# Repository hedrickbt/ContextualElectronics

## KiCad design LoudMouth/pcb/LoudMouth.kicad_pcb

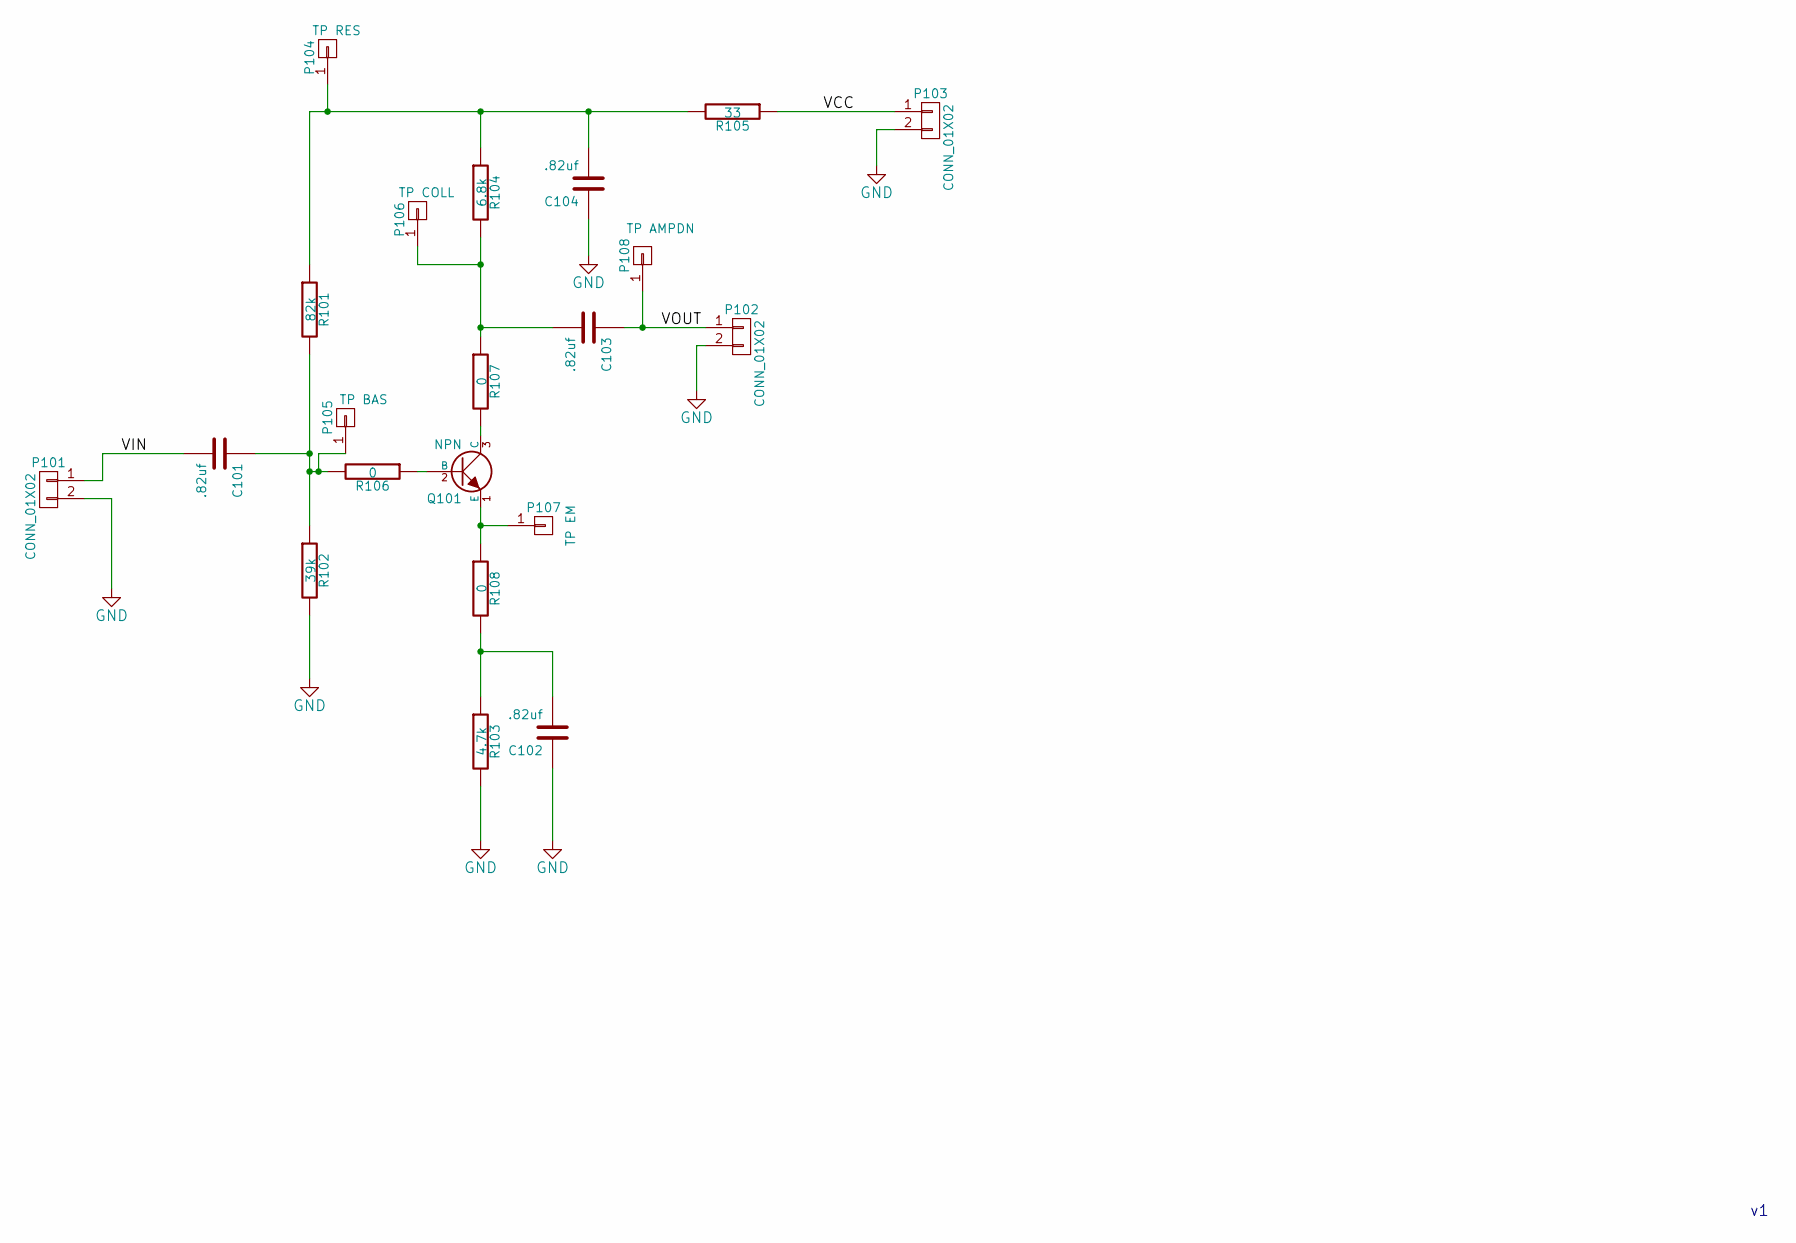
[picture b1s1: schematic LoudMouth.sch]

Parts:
C101, C102: .82uf; C_1210_HandSoldering; MPN Value
C103, C104: .82uf; C_1210_HandSoldering
P101, P102, P103: CONN_01X02; Pin_Header_Straight_1x02
P104: TP RES; TESTPOINT_1
P105: TP BAS; TESTPOINT_1
P106: TP COLL; TESTPOINT_1
P107: TP EM; TESTPOINT_1
P108: TP AMPDN; TESTPOINT_1; MPN Value
Q101: NPN; TO-92_Molded_Narrow
R101: 82k; R_0805_HandSoldering
R102: 39k; R_0805_HandSoldering; MPN Value
R103: 4.7k; R_0805_HandSoldering
R104: 6.8k; R_0805_HandSoldering
R105: 33; R_0805_HandSoldering
R106, R108: 0; R_0805_HandSoldering; MPN Value
R107: 0; R_0805_HandSoldering

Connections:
/VCC: P103.1, R105.1
/VIN: C101.2, P101.1
/VOUT: C103.1, P102.1, P108.1
GND: C102.1, C104.1, P101.2, P102.2, P103.2, R102.2, R103.2
unnamed: C101.1, P105.1, R101.2, R102.1, R106.2
unnamed: C102.2, R103.1, R108.2
unnamed: C103.2, P106.1, R104.2, R107.1
unnamed: C104.2, P104.1, R101.1, R104.1, R105.2
unnamed: P107.1, Q101.1 (E), R108.1
unnamed: Q101.2 (B), R106.1
unnamed: Q101.3 (C), R107.2

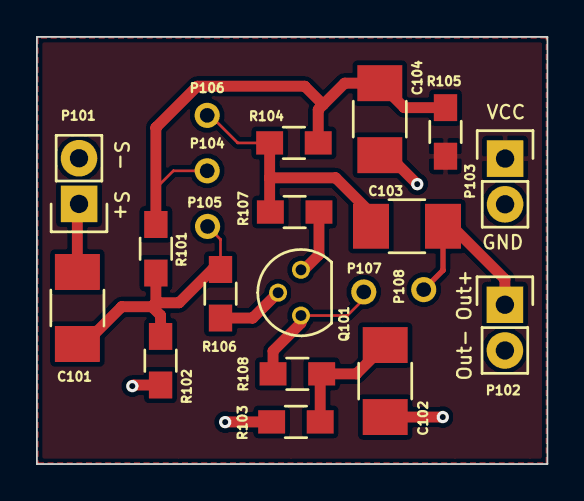
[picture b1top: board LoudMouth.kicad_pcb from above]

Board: 2 copper layers, 28.4 x 23.7 mm, 21 parts (0 on the bottom side), 11 nets.

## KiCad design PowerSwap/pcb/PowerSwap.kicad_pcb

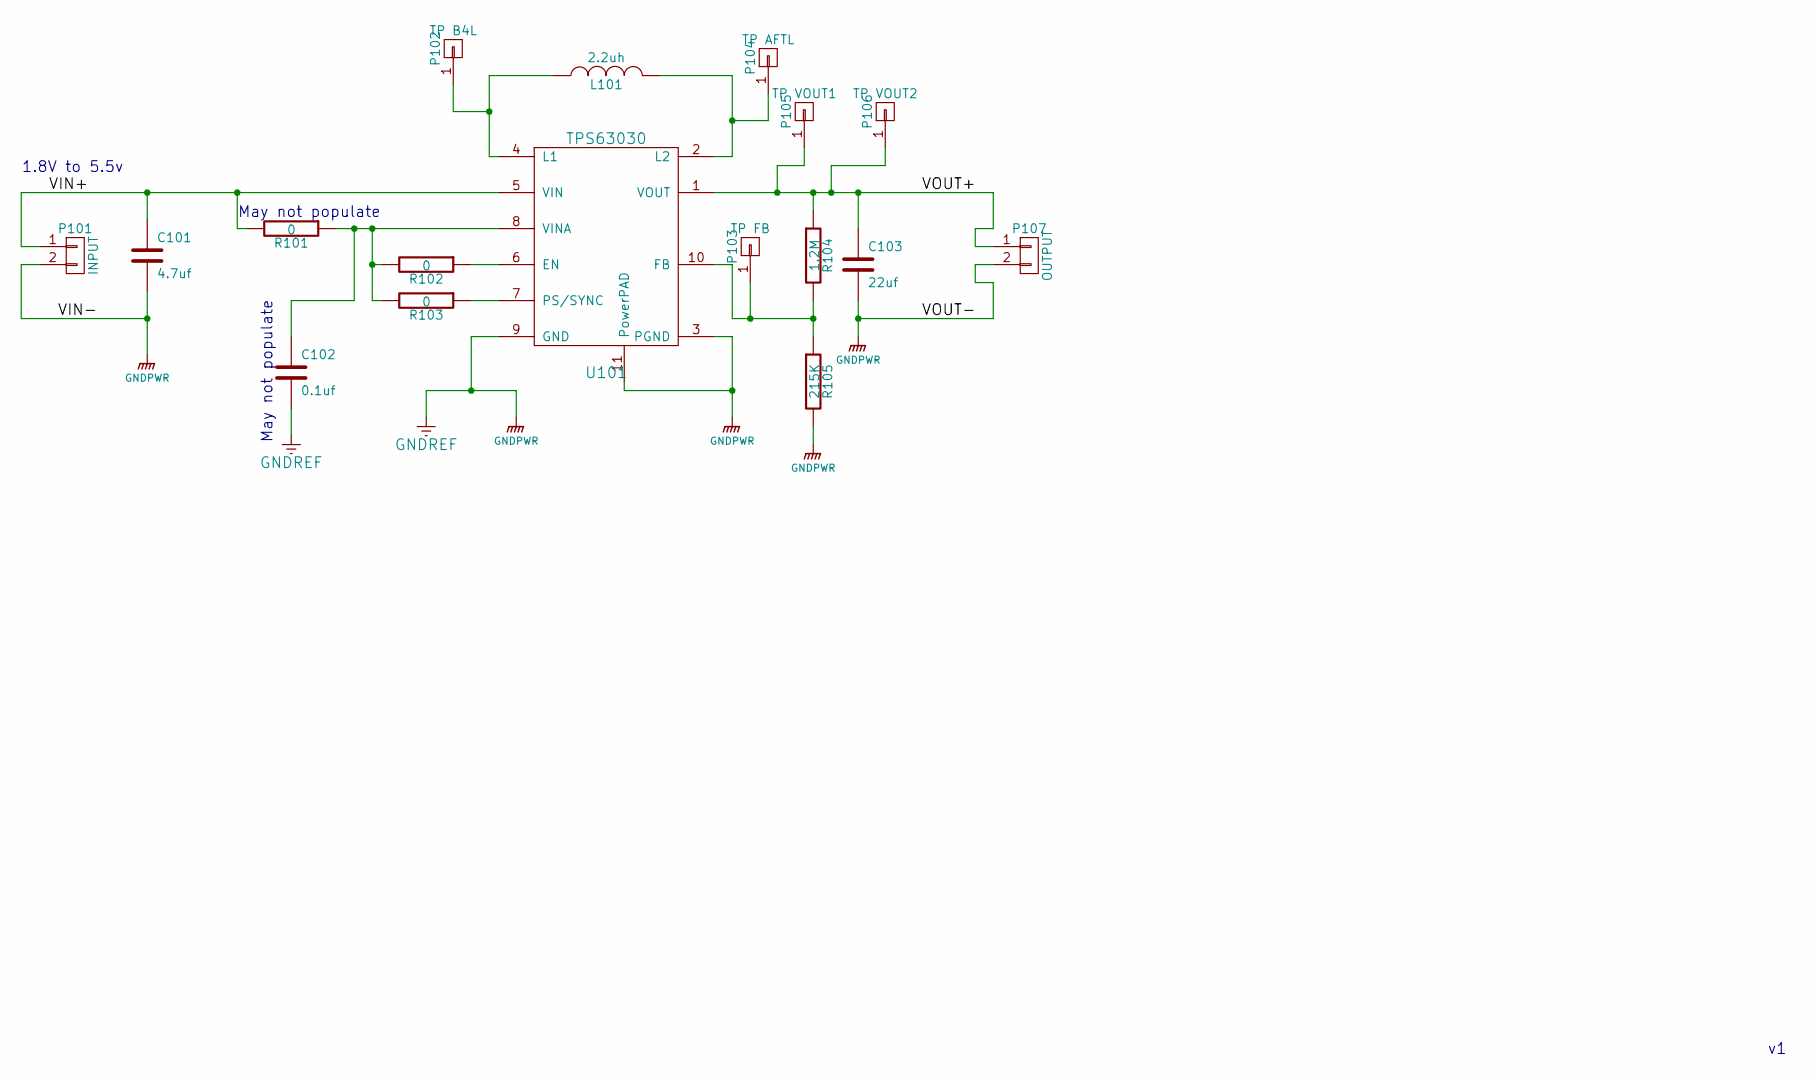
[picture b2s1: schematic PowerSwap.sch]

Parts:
C101: 4.7uf; MPN Value
C102: 0.1uf; MPN Value
C103: 22uf; MPN Value
L101: 2.2uh; LQH3NPN2R2NG0; MPN LQH3NPN2R2NG0
P101: INPUT
P102: TP B4L
P103: TP FB
P104: TP AFTL
P105: TP VOUT1
P106: TP VOUT2
P107: OUTPUT
R101: 0; MPN Value
R102, R103: 0
R104: 1.2M; MPN Value
R105: 215K
U101: TPS63030; SON10_HandSoldered_TPS63030

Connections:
/VIN+: C101.1, P101.1, R101.2, U101.5 (VIN)
/VOUT+: C103.1, P105.1, P106.1, P107.1, R104.1, U101.1 (VOUT); also elsewhere on the board
GNDPWR: C101.2, C102.2, C103.2, P101.2, P107.2, R105.2, U101.3 (PGND), U101.9 (GND), U101.11 (PowerPAD); also elsewhere on the board
unnamed: C102.1, R101.1, R102.2, R103.2, U101.8 (VINA)
unnamed: L101.1, P102.1, U101.4 (L1)
unnamed: L101.2, P104.1, U101.2 (L2)
unnamed: P103.1, R104.2, R105.1, U101.10 (FB)
unnamed: R102.1, U101.6 (EN)
unnamed: R103.1, U101.7 (PS/SYNC)

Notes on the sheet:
1.8V to 5.5v
May not populate

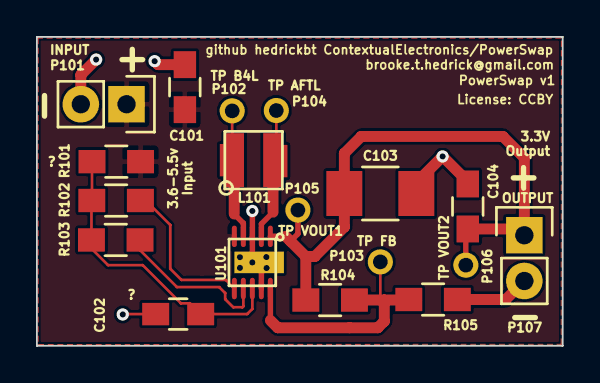
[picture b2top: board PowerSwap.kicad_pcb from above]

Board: 2 copper layers, 29.2 x 17.2 mm, 18 parts (0 on the bottom side), 9 nets.

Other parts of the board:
C104: uf; C_0805_HandSoldering

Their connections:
/VOUT+: C104.1; also elsewhere on the board
GNDPWR: C104.2; also elsewhere on the board

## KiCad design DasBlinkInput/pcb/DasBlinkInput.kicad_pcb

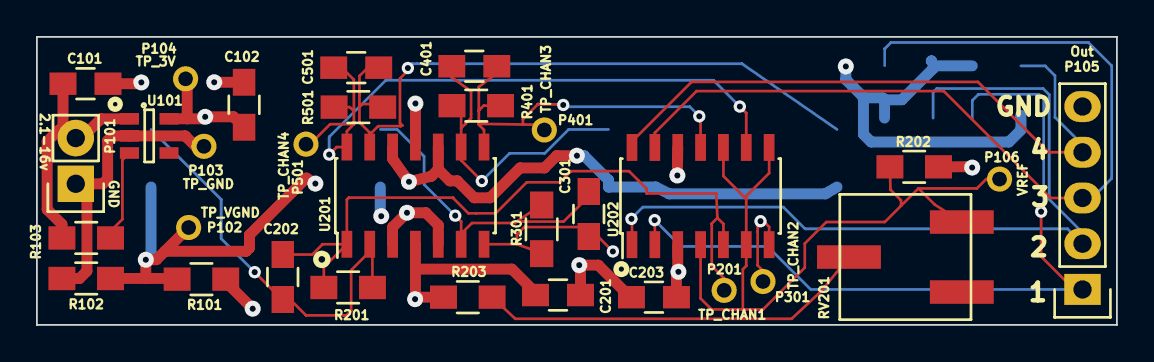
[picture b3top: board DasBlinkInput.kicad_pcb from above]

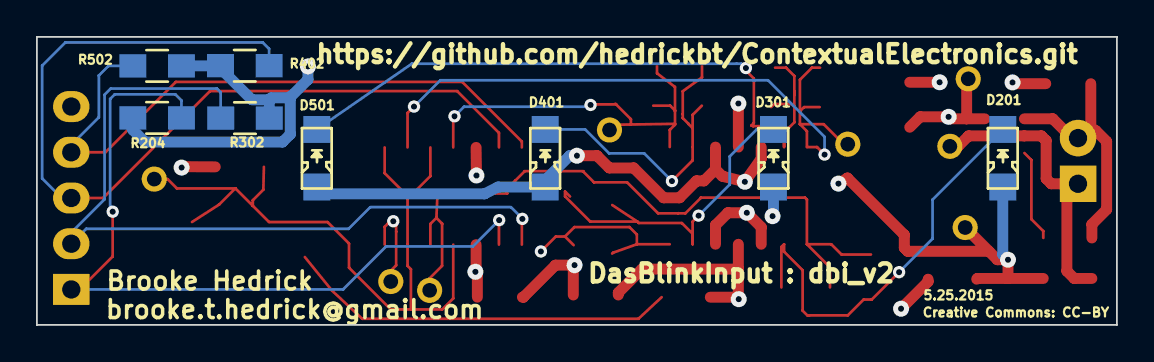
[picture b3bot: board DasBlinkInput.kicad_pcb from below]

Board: 4 copper layers, 60.0 x 16.0 mm, 39 parts (8 on the bottom side), 19 nets.

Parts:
C101, C102: 1uf; C_0805_HandSoldering
C201, C203: .1uf; C_0805_HandSoldering
C202, C301, C401, C501: 100pf; C_0805_HandSoldering
D201, D301, D401, D501: SFH 2701; SFH2701
P101: CONN_01X02; Pin_Header_Straight_1x02
P102: TP_VGND; TESTPOINT_1
P103: TP_GND; TESTPOINT_1
P104: TP_3V; TESTPOINT_1
P105: CONN_01X05; Pin_Header_Straight_1x05
P106: VREF; TESTPOINT_1
P201: TP_CHAN1; TESTPOINT_1
P301: TP_CHAN2; TESTPOINT_1
P401: TP_CHAN3; TESTPOINT_1
P501: TP_CHAN4; TESTPOINT_1
R101, R102, R202, R204, R302, R402, R502: 10K; R_0805_HandSoldering
R103, R203: 0; R_0805_HandSoldering
R201, R301, R401, R501: 1MEG; R_0805_HandSoldering
RV201: 10K; BOURNS_3361P
U101: LP2980-N; SOT-23-5
U201: MCP6404; SOIC-14_3.9x8.7mm_Pitch1.27mm
U202: LM339; SOIC-14_3.9x8.7mm_Pitch1.27mm

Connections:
3V: C102.1, C201.2, C203.2, P104.1, R101.1, R203.1, R204.1, R302.1, R402.1, R502.1, U101.5, U201.4, U202.3
/Channel1Photodetect/CHAN1_OUT: P105.1, R204.2, U202.2
/Channel2Photodetect/CHAN2_OUT: P105.2, R302.2, U202.1
/Channel2Photodetect/REF_IN: P106.1, R202.1, RV201.3, U202.4, U202.6, U202.8, U202.10
/Channel3Photodetect/CHAN3_OUT: P105.3, R402.2, U202.13
/Channel4Photodetect/CHAN4_OUT: P105.4, R502.2, U202.14
GND: C101.2, C102.2, C201.1, C203.1, P101.1, P103.1, P105.5, R102.2, R202.2, U101.2, U201.11, U202.12
unnamed: C101.1, P101.2, R103.1, U101.1
unnamed: C202.1, P201.1, R201.1, U201.1, U202.5
unnamed: C202.2, D201.2, R201.2, U201.2
unnamed: C301.1, P301.1, R301.1, U201.7, U202.7
unnamed: C301.2, D301.2, R301.2, U201.6
unnamed: C401.1, P401.1, R401.1, U201.8, U202.11
unnamed: C401.2, D401.2, R401.2, U201.9
unnamed: C501.1, P501.1, R501.1, U201.14, U202.9
unnamed: C501.2, D501.2, R501.2, U201.13
unnamed: R103.2, U101.3
unnamed: R203.2, RV201.2
VGND: D201.1, D301.1, D401.1, D501.1, P102.1, R101.2, R102.1, U201.3, U201.5, U201.10, U201.12

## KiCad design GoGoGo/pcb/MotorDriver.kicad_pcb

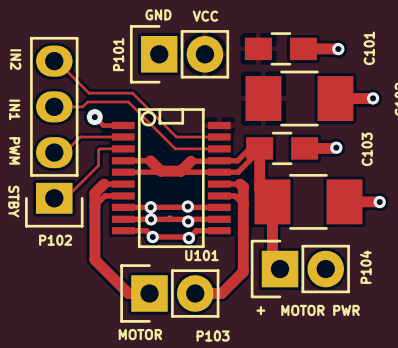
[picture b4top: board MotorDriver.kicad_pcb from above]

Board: 2 copper layers, 9 parts (0 on the bottom side), 9 nets.

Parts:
C101, C103: 0.1uf; C_0805_HandSoldering
C102, C104: 10uf; C_1210_HandSoldering
P101, P103, P104: CONN_01X02; Pin_Header_Straight_1x02
P102: CONN_01X04; Pin_Header_Straight_1x04
U101: TB6593FNG; SSOP-20

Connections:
/IN1: P102.3, U101.18
/IN2: P102.4, U101.19
/M+: P103.1, U101.6, U101.7
/PM+: C103.1, C104.1, P104.1, U101.4, U101.5, U101.16, U101.17
/PWM: P102.2, U101.2
/STBY: P102.1, U101.3
GND: C101.2, C102.2, C103.2, C104.2, P101.1, P104.2, U101.1, U101.8, U101.9, U101.10, U101.11, U101.12, U101.13
unnamed: C101.1, C102.1, P101.2, U101.20
unnamed: P103.2, U101.14, U101.15

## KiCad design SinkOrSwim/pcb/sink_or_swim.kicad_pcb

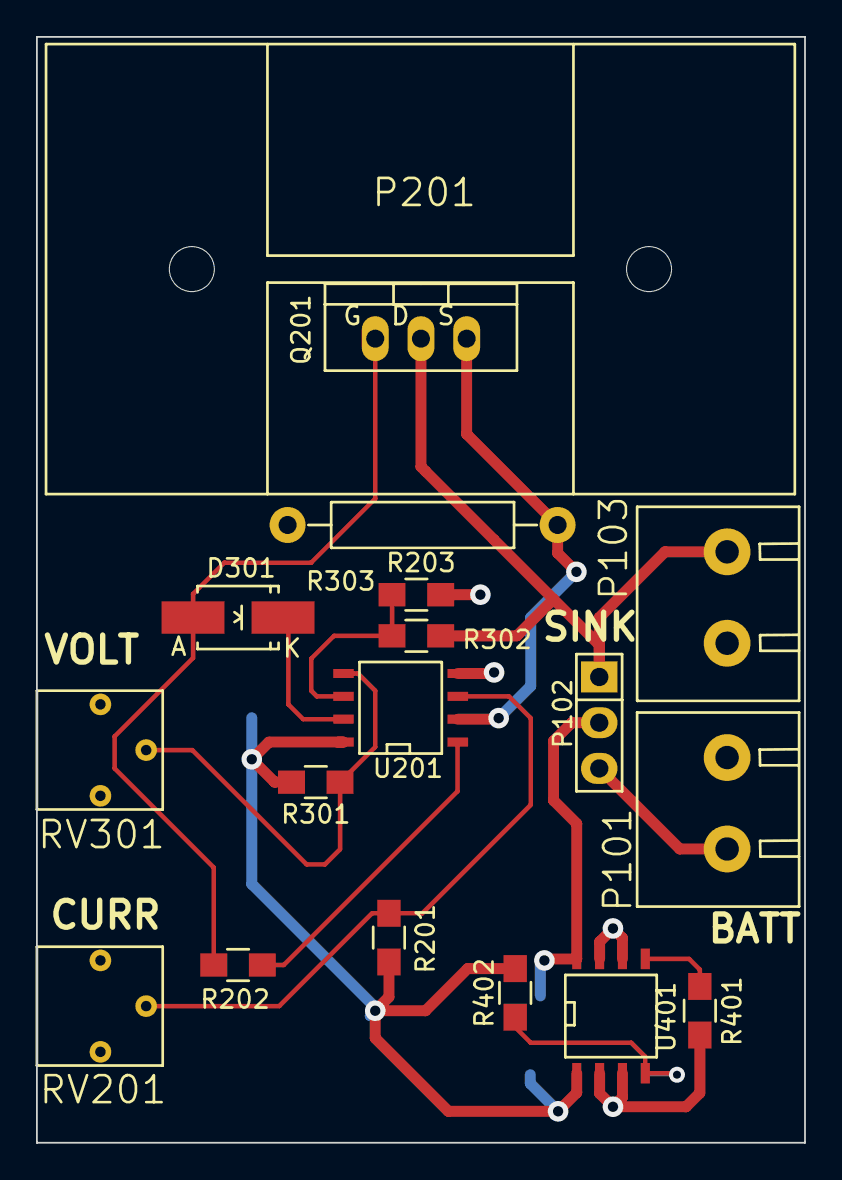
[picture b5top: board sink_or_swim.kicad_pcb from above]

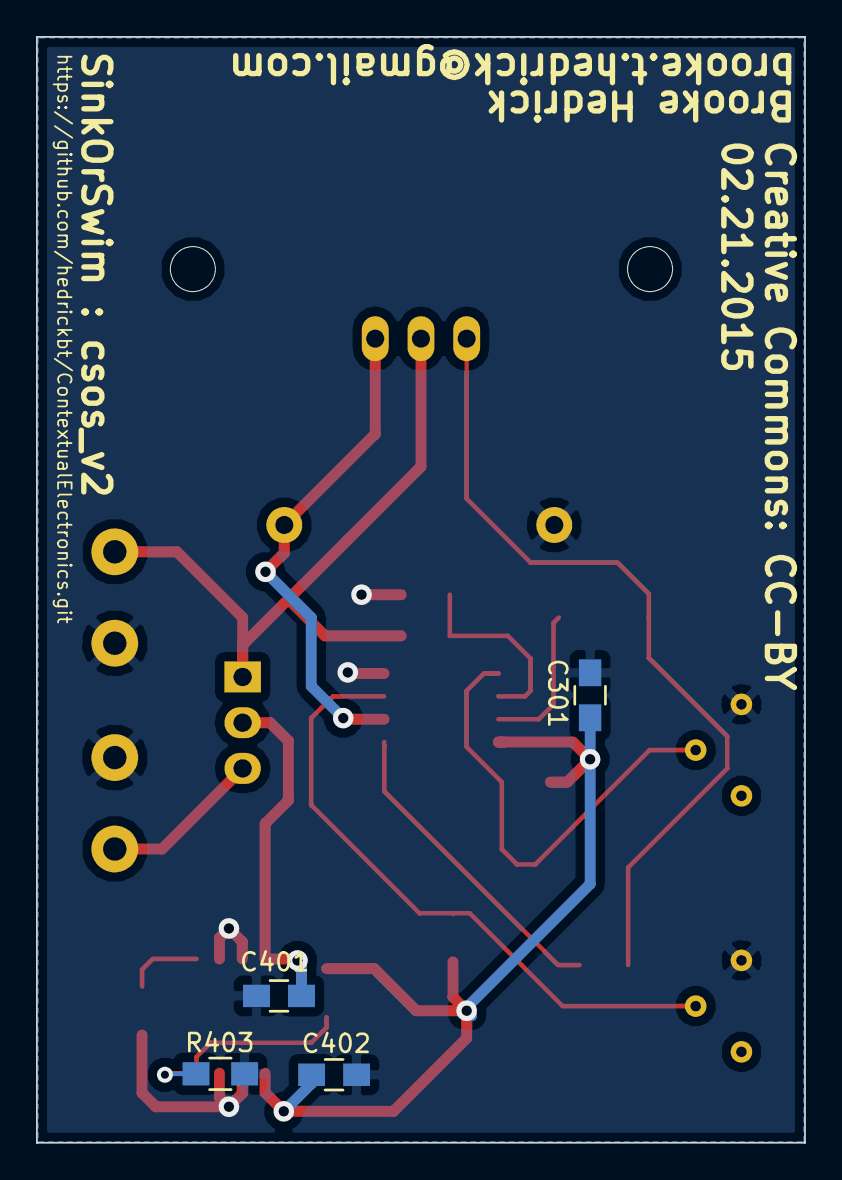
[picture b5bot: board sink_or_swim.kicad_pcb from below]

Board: 2 copper layers, 42.7 x 61.4 mm, 22 parts (4 on the bottom side), 14 nets.

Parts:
C301, C401, C402: .1uf; C_0805_HandSoldering
D301: DIODE; Diode-SMA_Handsoldering
P101, P103: TERMINAL_BLOCK; OSTTA024163
P102: CONN_01X03; Pin_Header_Straight_1x03
P201: HEATSINK; FA-T220-38E
Q201: BUK9575-100A; TO-220_FET-GDS_Vertical
R201: 68K; R_0805_HandSoldering
R202, R303: 1K; R_0805_HandSoldering
R203: .1; Resistor_Horizontal_RM15mm
R301: 28.7K; R_0805_HandSoldering
R302: 9K; R_0805_HandSoldering
R401: 0; R_0805_HandSoldering
R402: 27K; R_0805_HandSoldering
R403: 21.6K; R_0805_HandSoldering
RV201, RV301: 10K; Potiometer_Bourns_3362P
U201: LMV358; SOIC-8-N
U401: LM2931; SOIC-8-N

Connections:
2.7V: C301.1, C402.1, R201.1, R301.1, R402.2, U201.8, U401.1
/CurrentControl/Current_Sink+: P102.1, P103.2, Q201.D, R302.1
/CurrentControl/FET_Gate: D301.1, Q201.G, R202.1
/Power Regulation/Vin: C401.1, P102.2, U401.8
GND: C301.2, C401.2, C402.2, P101.2, P103.1, R203.2, R303.2, R401.2, R403.2, RV201.3, RV301.3, U201.4, U401.2, U401.3, U401.6, U401.7
unnamed: D301.2, U201.7
unnamed: P101.1, P102.3
unnamed: Q201.S, R203.1, U201.2
unnamed: R201.2, RV201.2, U201.3
unnamed: R202.2, U201.1
unnamed: R301.2, RV301.2, U201.5
unnamed: R302.2, R303.1, U201.6
unnamed: R401.1, U401.5
unnamed: R402.1, R403.1, U401.4

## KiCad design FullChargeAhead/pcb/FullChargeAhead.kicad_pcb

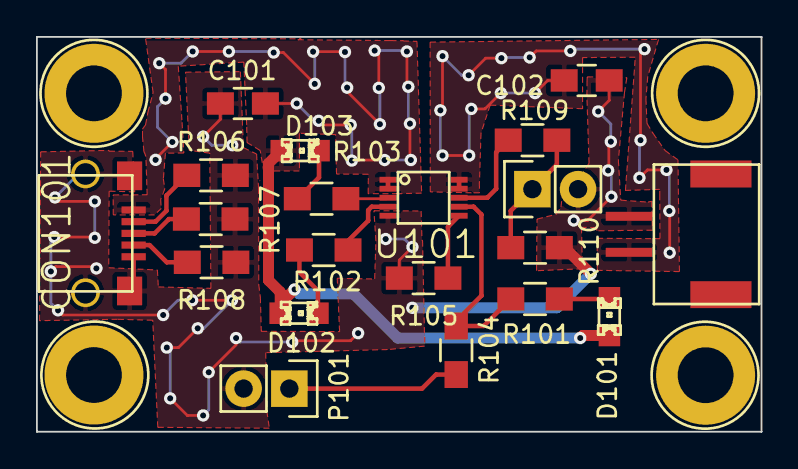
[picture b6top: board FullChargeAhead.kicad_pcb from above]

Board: 2 copper layers, 40.3 x 21.9 mm, 24 parts (0 on the bottom side), 16 nets.

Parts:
C101, C102: 4.7uf; C_0805_HandSoldering
CON101: USB-MICRO-B; MICRO_B_CONN_10118193-0001LF
D101: NOPOP; LED-0805
D102, D103: LED; LED-0805
P101: TIMER; Pin_Header_Straight_1x02
P102: BATT; JST_2pin_lipo_S2B-PH-SM4-TB
P103, P104, P105, P106: CONN_01X01; 1pin_m3_screw
P107: THERM; Pin_Header_Straight_1x02
R101, R106, R107, R108: NOPOP; R_0805_HandSoldering
R102, R103: 470; R_0805_HandSoldering
R104: 1K; R_0805_HandSoldering
R105: 2K; R_0805_HandSoldering
R109: 1.54K; R_0805_HandSoldering
R110: 69.8K; R_0805_HandSoldering
U101: MCP73834-FCI/UN; MSOP-10

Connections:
/Vbat: C102.1, P102.1, U101.9, U101.10
/Vdd: C101.1, CON101.1, D101.1, D102.1, D103.1, U101.1, U101.2
GND: C101.2, C102.2, CON101.5, CON101.6, CON101.7, CON101.8, CON101.9, P101.2, P102.2, P107.2, R105.2, R106.1, R107.1, R108.1, R110.2, U101.5
unnamed: CON101.2, R106.2
unnamed: CON101.3, R107.2
unnamed: CON101.4, R108.2
unnamed: D101.2, R101.2
unnamed: D102.2, R102.2
unnamed: D103.2, R103.2
unnamed: P101.1, R104.1
unnamed: P107.1, R109.2, R110.1
unnamed: R101.1, R104.2, U101.7
unnamed: R102.1, U101.4
unnamed: R103.1, U101.3
unnamed: R105.1, U101.6
unnamed: R109.1, U101.8

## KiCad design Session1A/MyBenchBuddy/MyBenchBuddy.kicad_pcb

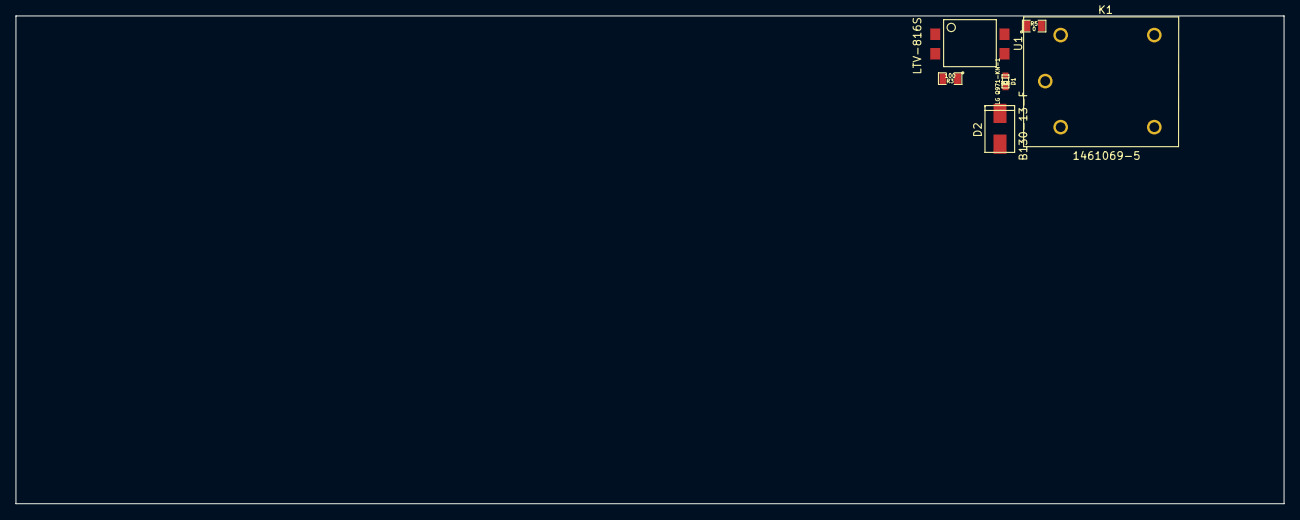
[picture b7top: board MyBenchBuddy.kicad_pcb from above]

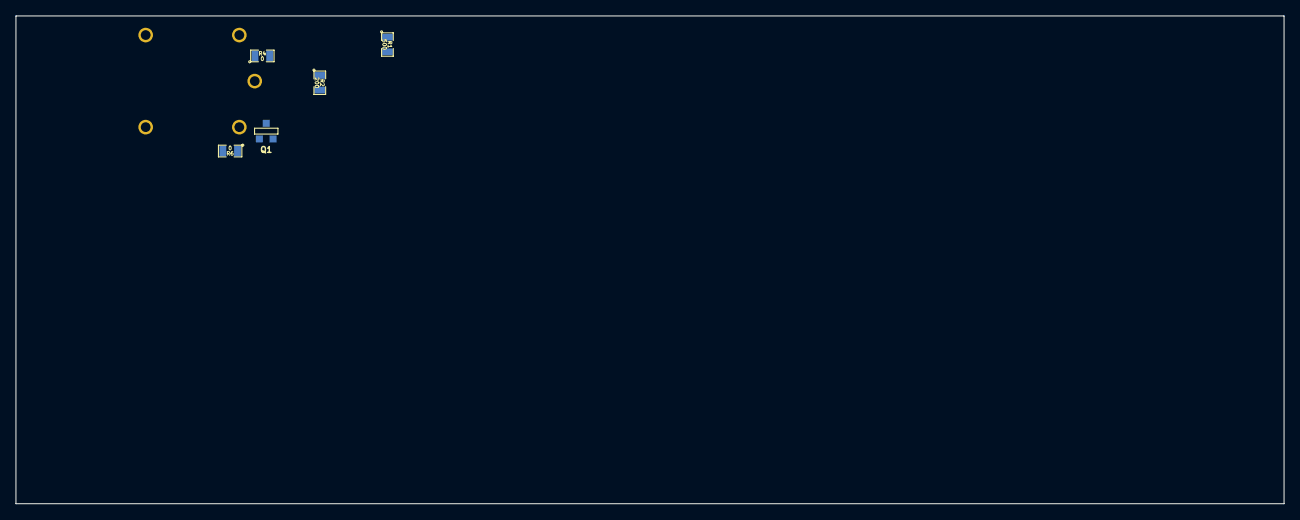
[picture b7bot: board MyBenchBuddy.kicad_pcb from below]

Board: 2 copper layers, 165.1 x 63.5 mm, 11 parts (5 on the bottom side), 10 nets, no tracks yet.

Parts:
D1: LG Q971-KN-1; LED-0603
D2: B130-13-F; SMA
K1: 1461069-5; TE-ORWH-RELAY
Q1: 2N3904; SOT23EBC
R1: 500; SM0805
R2: 200; SM0805
R3: 100; SM0805
R4, R5, R6: 0; SM0805
U1: LTV-816S; 4-SMD

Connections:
+12P: R4.1, R5.1
GND: R2.2, R6.2
unnamed: R1.2, U1.2
unnamed: R4.2, U1.4
unnamed: D2.2, K1.2, R5.2
unnamed: D2.1, K1.5, Q1.3
unnamed: D1.2, R2.1
unnamed: Q1.1, R6.1
unnamed: Q1.2, R3.2
unnamed: D1.1, R3.1, U1.3

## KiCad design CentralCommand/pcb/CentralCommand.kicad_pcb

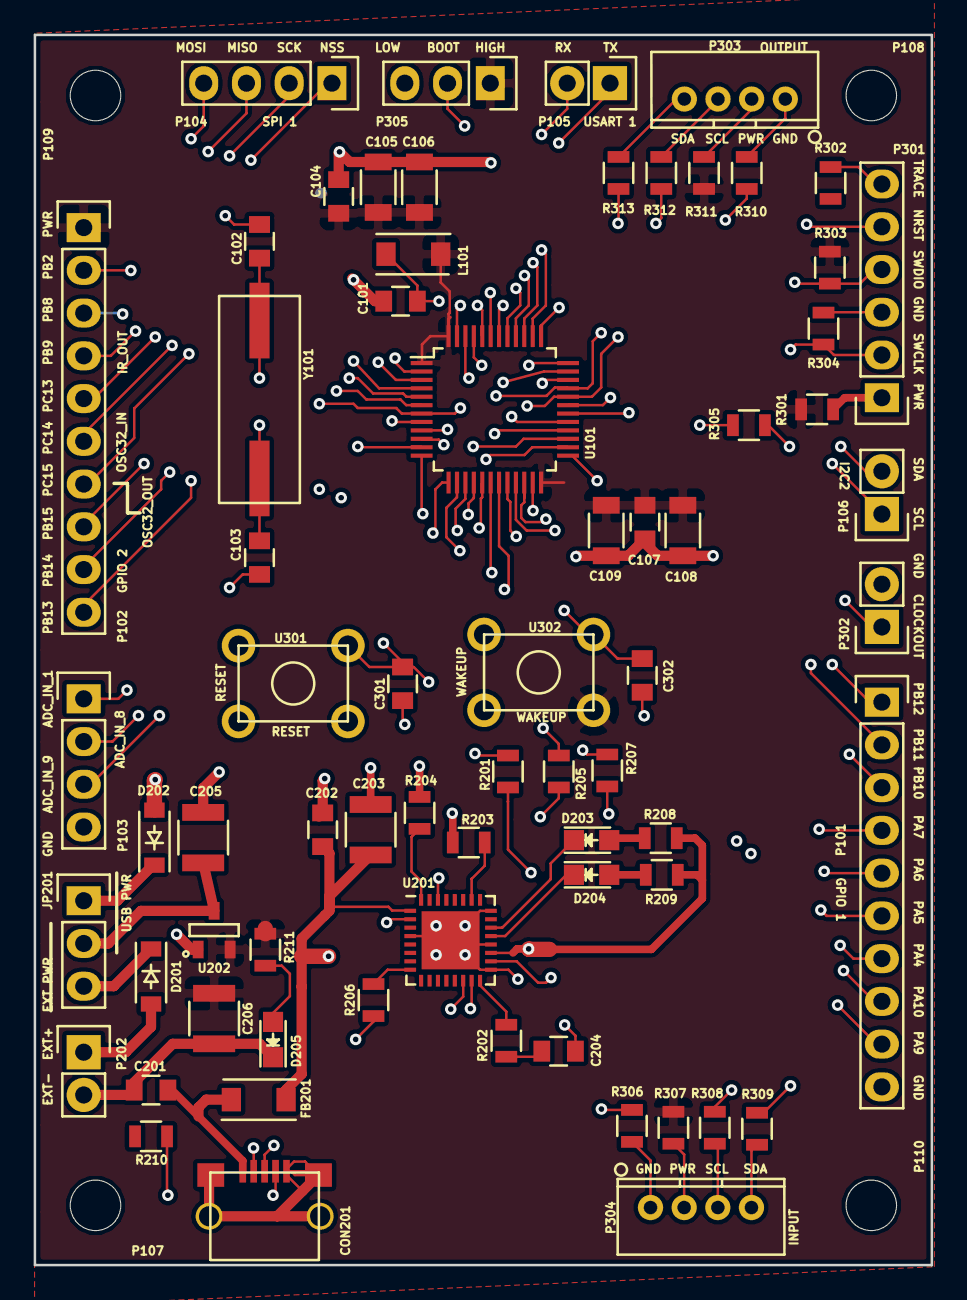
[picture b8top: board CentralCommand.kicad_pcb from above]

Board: 4 copper layers, 53.3 x 73.1 mm, 72 parts (0 on the bottom side), 77 nets.

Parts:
C101: C; C_0805
C102, C103: 18pf; C_0805
C104, C107: 0.1u; C_0805
C105, C108: 1u; C_1206
C106, C109: 10u; C_1206
C201: 10nf; C_0805
C202, C204: 100nf; C_0805
C203: 4.7uf; C_1210
C205, C206: 10uf; C_1210
C301, C302: 0.1uf; C_0805
CON201: USB-MICRO-B; MICRO_B_CONN_10118193-0001LF
D201, D202: D_Schottky; SOD-123
D203, D204, D205: LED; LED_0805
FB201: FILTER; Neosid_Inductor_SM1206
JP201: JUMPER3; Pin_Header_Straight_1x03
L101: INDUCTOR; Neosid_Inductor_SM1206
P101, P102: CONN_01X10; Pin_Header_Straight_1x10
P103, P104: CONN_01X04; Pin_Header_Straight_1x04
P105, P106, P202, P302: CONN_01X02; Pin_Header_Straight_1x02
P107, P108, P109, P110: CONN_01X01; MountingHole_3mm
P301: CONN_01X06; Pin_Header_Straight_1x06
P303, P304: CONN_01X04; GroveConnectorStraight_B4B-PH-K-S
P305: CONN_01X03; Pin_Header_Straight_1x03
R201, R202, R203, R205, R207, R301, R302, R306, R307, R308, R309, R310, R311, R312, R313: 0; R_0805
R204, R206, R210: NOP; R_0805
R208, R209, R211: 270; R_0805
R303, R304: 100k; R_0805
R305: R; R_0805
U101: STM32F030C8; LQFP-48_7x7mm_Pitch0.5mm
U201: FT232RQ; QFN-32-1EP_5x5mm_Pitch0.5mm
U202: MCP1700T-3302E/TT; SOT-23
U301, U302: B3F-1020; Pushbutton_B3F-1020
Y101: Crystal; Crystal_HC49_US

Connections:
/ADC_IN1: P103.1, U101.11
/ADC_IN8: P103.2, U101.18
/ADC_IN9: P103.3, U101.19
/Comm/BOOT0: P305.2, U101.44
/Comm/CLOCKOUT: P302.1, R305.2
/Comm/MC0: R305.1, U101.29
/Comm/NRST: C301.1, P301.5, R201.1, U101.7, U301.3
/Comm/PWR: C104.1, C105.1, C106.1, C107.1, C108.1, C109.1, C206.1, L101.1, P102.1, P305.1, R211.2, R301.1, R303.1, R307.2, R311.2, U101.1, U101.24, U101.48, U202.2, U302.1
/Comm/SCL: R308.2, R312.2, U101.32
/Comm/SDA: R309.2, R313.2, U101.33
/Comm/SWCLK: P301.2, R304.1, U101.37
/Comm/SWDIO: P301.4, R303.2, U101.34
/Comm/WKUP1: C302.1, U101.10, U302.3
/I2C2_SCL: P106.1, U101.35
/I2C2_SDA: P106.2, U101.36
/PA4: P101.7, U101.14
/PA5: P101.6, U101.15
/PA6: P101.5, U101.16
/PA7: P101.4, U101.17
/PA9: P101.9, U101.30
/PA10: P101.8, U101.31
/PB2: P102.2, U101.20
/PB8: P102.3, U101.45
/PB9: P102.4, U101.46
/PB10: P101.3, U101.21
/PB11: P101.2, U101.22
/PB12: P101.1, U101.25
/PB13: P102.10, U101.26
/PB14: P102.9, U101.27
/PB15: P102.8, U101.28
/PC13: P102.5, U101.2
/PC14: P102.6, U101.3
/PC15: P102.7, U101.4
/Power/EXT_PWR: D201.1, JP201.3
/Power/RXD: R207.2, U101.13
/Power/TXD: R205.2, U101.12
/Power/USB_PWR: D202.1, JP201.1
/Power/VCC: C202.2, C203.2, D202.2, FB201.2, R208.1, R209.1, U201.1, U201.19
/SPI1_MISO: P104.3, U101.40
/SPI1_MOSI: P104.4, U101.41
/SPI1_NSS: P104.1, U101.38
/SPI1_SCK: P104.2, U101.39
/USART1_RX: P105.2, U101.43
/USART1_TX: P105.1, U101.42
/VDDA: C101.1, L101.2, U101.9
GND: C101.2, C102.1, C103.1, C104.2, C105.2, C106.2, C107.2, C108.2, C109.2, C201.1, C202.1, C203.1, C204.2, C205.2, C206.2, C301.2, C302.2, CON201.5, CON201.6, CON201.7, CON201.8, CON201.9, D205.1, P101.10, P103.4, P202.2, P301.3, P302.2, P305.3, R203.2, R204.1, R206.1, R304.2, R306.2, R310.2, U101.8, U101.23, U101.47, U201.4, U201.17, U201.20, U201.24, U201.33, U202.1, U301.1
unnamed: C102.2, U101.5, Y101.2
unnamed: C103.2, U101.6, Y101.1
unnamed: C201.2, CON201.1, FB201.1
unnamed: C204.1, R202.1
unnamed: C205.1, JP201.2, U202.3
unnamed: CON201.2, U201.15
unnamed: CON201.3, U201.14
unnamed: CON201.4, R210.2
unnamed: D201.2, P202.1
unnamed: D203.1, U201.22
unnamed: D203.2, R208.2
unnamed: D204.1, U201.21
unnamed: D204.2, R209.2
unnamed: D205.2, R211.1
unnamed: P301.1, R301.2
unnamed: P301.6, R302.1
unnamed: P303.1, R310.1
unnamed: P303.2, R311.1
unnamed: P303.3, R312.1
unnamed: P303.4, R313.1
unnamed: P304.1, R306.1
unnamed: P304.2, R307.1
unnamed: P304.3, R308.1
unnamed: P304.4, R309.1
unnamed: R201.2, U201.18
unnamed: R202.2, U201.16
unnamed: R203.1, U201.26
unnamed: R204.2, U201.32
unnamed: R205.1, U201.30
unnamed: R206.2, U201.8
unnamed: R207.1, U201.2

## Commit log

2013-09-05 Initial
2013-09-08 Module 2 Unit 11
2013-09-13 Module 2 Unit 9
2013-09-20 Module2Unit11
2013-09-20 Module3Unit3
2013-09-25 Module3Unit4
2013-09-28 Module3Unit5
2013-10-08 GettingToBlinky
2013-10-09 Thermocouple TerminalBlock Fan Relay GTB PowerAdjustmentMonitor
2013-10-09 Brought some more pins up to the top sheet.
2014-02-03 Initial project setup
2014-02-03 Creating a Schematic Skeleton
2014-02-04 Defining Your Inputs and Outputs
2014-02-05 Understanding The Thermocouple Module
2014-02-09 Understanding The Current/Fan Driver Module
2014-02-09 Understanding The Relay Module
2014-02-11 Understanding The Power Protection and Filtering Module
2014-02-13 Understanding The Power Control, Conditioning, And Monitoring Module
2014-02-13 Understanding the LED Driver Module
2014-02-13 Understanding_the_LED_Driver_Module
2014-02-26 Understanding the Arduino Module
2014-03-01 Revisiting The Current/Fan Module
2015-02-05 update parts
2015-02-11 Fair number of parts are filled out now. Schematic allows for separate power source.
2015-02-12 Added Hiearchical Sheets and Power Burn
2015-02-14 First annotation
2015-02-14 Footprints associated and parts on pcb
2015-02-15 Fixed some drc items and started on heatsink footprint.
2015-02-15 Finished heatsink footprint and first stab at pcb layout.
2015-02-17 Find new terminal blocks. Set resistor divider values. Rearrange POT and fixed resistor.
2015-02-18 Switched pin headers for terminal blocks for batt and self-powered from sink. PCB is WIP.
2015-02-18 Small layout changes.
2015-02-18 Hide some of the labels on the pcb. Moved the ground plane to the bottom. More work reconnecting to do.
2015-02-19 More pcb layout changes. Looks better now.
2015-02-20 Updated Design Rules for power on pcb and redrew some traces.
2015-02-21 Better Layout. Added 2 1x2 pin headers to be able to test current.
2015-02-21 Testing a tag csos_v1
2015-02-21 Testing csos_v1 tag again
2015-02-21 Labeling the pcb
2015-02-23 Hid some more labels on pcb
2015-02-25 Generate gerbers and set correct hole sizes for potentiometer
2015-03-03 Gerbers added, BOM written
2015-03-08 BBEE Finished Module 5 assembly through reversing SPI pins
2015-03-17 Catching up with changes - RWI model, CSOS blog, ...
2015-03-18 Initial FCA schematic and associations
2015-03-20 FCA final footprints and initial pcb layout w/out wires
2015-03-21 Added spreadsheet without c201 and cut trace
2015-03-24 Chart of input voltage vs amps. Also started getting ready for v2 changes.
2015-03-24 First board layout complete and initial gerbers.
2015-03-25 Gerbers renamed for oshpark and v1 is ready to go
2015-03-25 Ready to tag fca_v1
2015-03-25 Fix MicroB footprint. Cannot have plated slot. I had to change it to a larger circle.
2015-04-21 Adding pdfs for support docs and updated readme
2015-04-21 csos getting ready to send out for boards
2015-05-16 Catching up on items
2015-05-24 Progress on DBI schematic
2015-05-24 BB progress
2015-05-25 DBI : complete pcb
2015-05-26 Final DBI pcb changes
2015-06-11 adding .gitignore file
2015-06-11 added DBI BOM
2015-07-13 added notes
2015-07-20 Initial GGG MotorDriver schematic
2015-07-21 Merged changes
2015-07-21 MotorDriver pcb rough layout
2015-07-21 Increased GGG MotorDriver track widths
2015-07-21 Created gerbers for GGG Motor Driver
2015-07-21 Added status for GGG and cleaned up some dup gerber files
2015-07-21 added TB6593FNG docs for GGG
2015-07-23 Restructuring folders to accomodate multiple boards
2015-07-23 Process deletes from move
2015-07-23 GGG MotorEncoder schematic added
2015-07-23 GGG MotorEncoder schematic updated with missing video items
2015-07-23 GGG MotorEncoder begin to associate footprints
2015-07-23 GGG MotorEncoder added encoder footprint and associated
2015-07-23 GGG MotorEncoder imported testpoint footprint
2015-07-23 GGG MotorEncoder final pcb submitted to OSH Park
2015-07-25 GGG Motor Driver : fixed an issue with the library path
2015-07-27 DBI - fixed reg/on pin, changed resistor to 0 ohm near divider and rv, added 10k pull up resistors to 3V for each output channel.
2015-07-29 Setting up PowerSwap project. PS
2015-08-01 PS created schematic
2015-08-01 PS updated schematic with testpoints and option a/b applications
2015-08-02 PS added PowerPAD to tps6030, created footprint for tps6030
2015-08-03 GGG updated status
2015-08-03 PS annotated and generated netlist
2015-08-07 PS : beginning of inductor equations
2015-08-08 PS : more equations
2015-08-08 GGG : Motor Encoder : changed R102 to 10K and started v2
2015-08-10 GGG : Added photos and created Arduino test for Motor Driver
2015-08-10 PS : updated status
2015-08-15 PS : starting inductor footprint
2015-08-15 PS : working on regulator footprint
2015-08-15 PS : associate and start pcb
2015-08-16 PS : first layout complete and gerbers generated
2015-08-16 PS : small pcb change
2015-08-17 PS : final pcb layout changes
2015-08-17 PS : pcb and stencil zip files along with new images
2015-08-21 GGG ENC : Created Encoder disk 3d part
2015-08-22 GGG ENC : photos of the 3d printed encoder wheel
2015-08-29 RWI LM GGG-ENC : Encoder test, Nucleo docs and firmware, Loudmouth spice
2015-09-05 GGG : motor driver tests, encoder calcs, and interrupt details. LM : Spice. PS : Status updates.
2015-09-18 LoudMouth initial PCB, PowerSwap testing documentation
2016-03-03 Catching up lots of changes

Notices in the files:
DasBlinkInput/pcb/DasBlinkInput.kicad_pcb:
Creative Commons: CC-BY
LoudMouth/pcb/LoudMouth.kicad_pcb:
License: CCBY
